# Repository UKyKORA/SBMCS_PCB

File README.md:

# Small Bot Motor Control Shield
This PCB makes building an advanced robot very simple. An onboard 32 bit ARM processor coordinates the control of 2 motors, as well as monitoring encoders on these motors for wheel odometry for the robot. There is a 9 axis IMU on the board to provide inertial odometry as well. a 5v @5A regulator provides enough power for most single board computers

### Board renders

### Assembled boards

### Demonstration

[https://youtu.be/KzK6t1kKt98](https://youtu.be/KzK6t1kKt98)

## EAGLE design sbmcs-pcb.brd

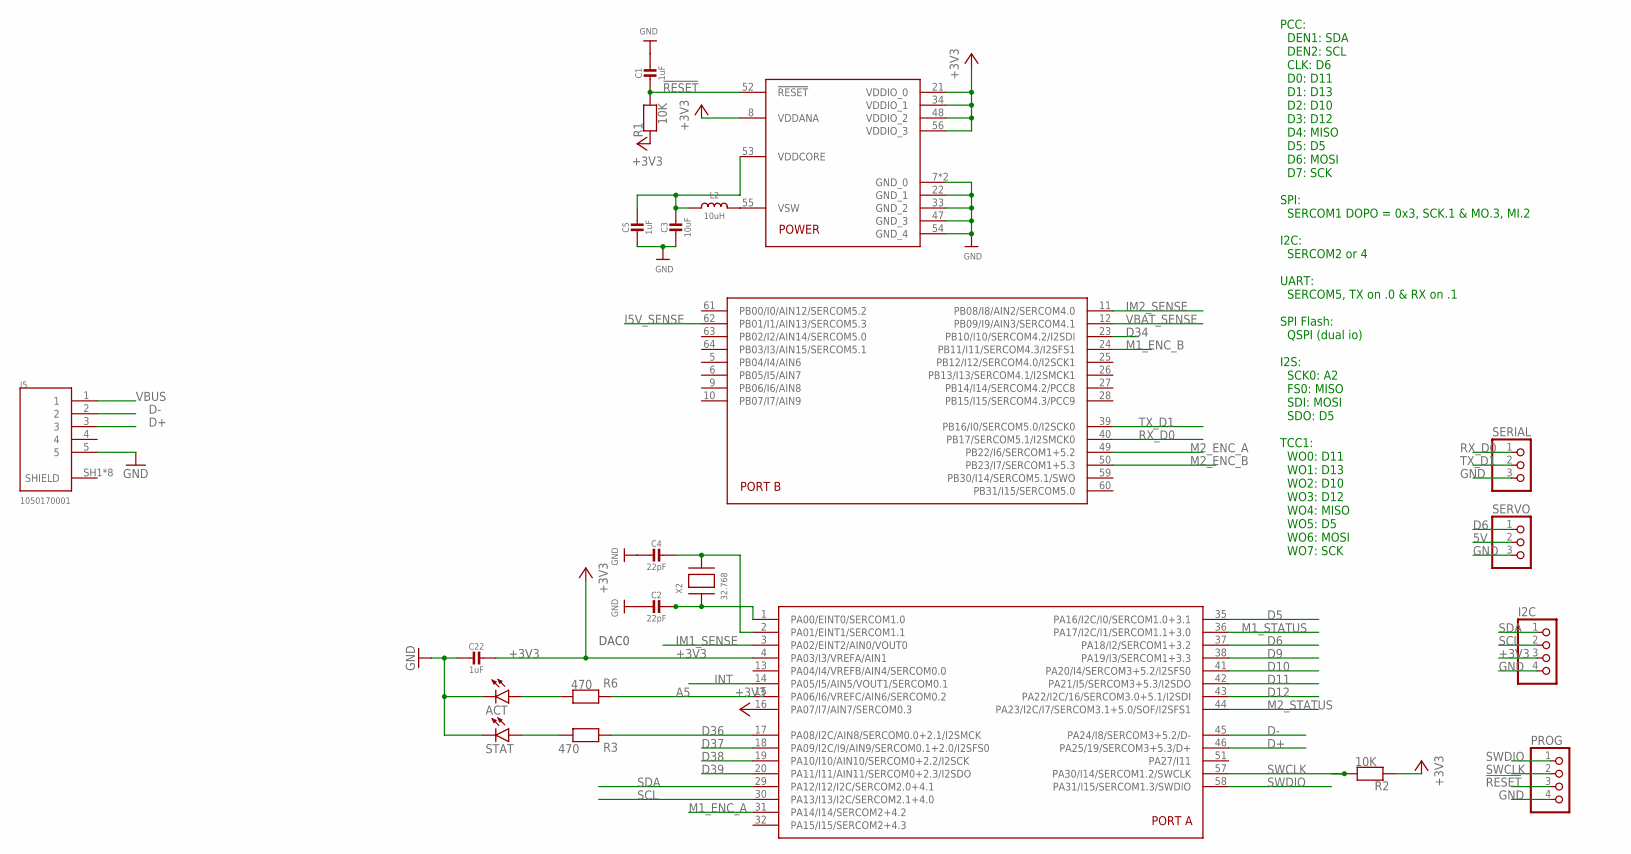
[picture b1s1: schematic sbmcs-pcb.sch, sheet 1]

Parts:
ACT: LEDCHIPLED_0805; CHIPLED_0805
C1, C5, C22: 1uF; 0603-NO
C2, C4: 22pF; 0603-NO
C3: 10uF; 0805-NO
I2C: PINHD-1X4; 1X04
J5: 1050170001; MOLEX_1050170001
L2: 10uH; INDUCTOR_1007
PROG: PINHD-1X4; 1X04
R1, R2: 10K; 0603-NO
R3, R6: 470; 0603-NO
SERIAL: PINHD-1X3; 1X03
SERVO: PINHD-1X3; 1X03
STAT: LEDCHIPLED_0805; CHIPLED_0805
U4: ATSAMD51J; PQFN64-1
X2: 32.768; XTAL3215

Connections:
5V: SERVO.2; also elsewhere on the board
!RESET: C1.2, PROG.3, R1.2, U4.52 (!RESET)
+3V3: C22.1, I2C.3, R1.1, R2.1, U4.4 (PA03/I3/VREFA/AIN1), U4.8 (VDDANA), U4.16 (PA07/I7/AIN7/SERCOM0.3), U4.21 (VDDIO_0), U4.34 (VDDIO_1), U4.48 (VDDIO_2), U4.56 (VDDIO_3); also elsewhere on the board
A5: R6.1, U4.15 (PA06/I6/VREFC/AIN6/SERCOM0.2)
D5: U4.35 (PA16/I2C/I0/SERCOM1.0+3.1)
D6: SERVO.1, U4.37 (PA18/I2/SERCOM1+3.2)
D9: U4.38 (PA19/I3/SERCOM1+3.3); also elsewhere on the board
D10: U4.41 (PA20/I4/SERCOM3+5.2/I2SFS0); also elsewhere on the board
D11: U4.42 (PA21/I5/SERCOM3+5.3/I2SDO); also elsewhere on the board
D12: U4.43 (PA22/I2C/16/SERCOM3.0+5.1/I2SDI); also elsewhere on the board
D34: U4.23 (PB10/I10/SERCOM4.2/I2SDI); also elsewhere on the board
D36: R3.1, U4.17 (PA08/I2C/AIN8/SERCOM0.0+2.1/I2SMCK)
D37: U4.18 (PA09/I2C/I9/AIN9/SERCOM0.1+2.0/I2SFS0); also elsewhere on the board
D38: U4.19 (PA10/I10/AIN10/SERCOM0+2.2/I2SCK); also elsewhere on the board
D39: U4.20 (PA11/I11/AIN11/SERCOM0+2.3/I2SDO); also elsewhere on the board
D+: J5.3, U4.46 (PA25/19/SERCOM3+5.3/D+)
D-: J5.2, U4.45 (PA24/I8/SERCOM3+5.2/D-)
GND: ACT.C, C1.1, C2.2, C3.2, C4.2, C5.2, C22.2, I2C.4, J5.5, PROG.4, SERIAL.3, SERVO.3, STAT.C, U4.7 (GND_0), U4.22 (GND_1), U4.33 (GND_2), U4.47 (GND_3), U4.54 (GND_4), U4.EXP (GND_0); also elsewhere on the board
I5V_SENSE: U4.62 (PB01/I1/AIN13/SERCOM5.3); also elsewhere on the board
IM1_SENSE: U4.3 (PA02/EINT2/AIN0/VOUT0); also elsewhere on the board
IM2_SENSE: U4.11 (PB08/I8/AIN2/SERCOM4.0); also elsewhere on the board
INT: U4.14 (PA05/I5/AIN5/VOUT1/SERCOM0.1); also elsewhere on the board
M1_ENC_A: U4.31 (PA14/I14/SERCOM2+4.2); also elsewhere on the board
M1_ENC_B: U4.24 (PB11/I11/SERCOM4.3/I2SFS1); also elsewhere on the board
M1_STATUS: U4.36 (PA17/I2C/I1/SERCOM1.1+3.0); also elsewhere on the board
M2_ENC_A: U4.49 (PB22/I6/SERCOM1+5.2); also elsewhere on the board
M2_ENC_B: U4.50 (PB23/I7/SERCOM1+5.3); also elsewhere on the board
M2_STATUS: U4.44 (PA23/I2C/I7/SERCOM3.1+5.0/SOF/I2SFS1); also elsewhere on the board
unnamed: R3.2, STAT.A
unnamed: ACT.A, R6.2
unnamed: C2.1, U4.1 (PA00/EINT0/SERCOM1.0), X2.P$1
unnamed: C4.1, U4.2 (PA01/EINT1/SERCOM1.1), X2.P$2
unnamed: L2.P$2 (2), U4.55 (VSW)
RX_D0: SERIAL.1, U4.40 (PB17/SERCOM5.1/I2SMCK0)
SCL: I2C.2, U4.30 (PA13/I13/I2C/SERCOM2.1+4.0); also elsewhere on the board
SDA: I2C.1, U4.29 (PA12/I12/I2C/SERCOM2.0+4.1); also elsewhere on the board
SWCLK: PROG.2, R2.2, U4.57 (PA30/I14/SERCOM1.2/SWCLK)
SWDIO: PROG.1, U4.58 (PA31/I15/SERCOM1.3/SWDIO)
TX_D1: SERIAL.2, U4.39 (PB16/I0/SERCOM5.0/I2SCK0)
VBAT_SENSE: U4.12 (PB09/I9/AIN3/SERCOM4.1); also elsewhere on the board
VBUS: J5.1; also elsewhere on the board
VDDCORE1: C3.1, C5.1, L2.P$1 (1), U4.53 (VDDCORE)

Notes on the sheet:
PCC: DEN1: SDA DEN2: SCL CLK: D6 D0: D11 D1: D13 D2: D10 D3: D12 D4: MISO D5: D5 D6: MOSI D7: SCK SPI: SERCOM1 DOPO = 0x3, SCK.1 & MO.3, MI.2 I2C: SERCOM2 or 4 UART: SERCOM5, TX on .0 & RX on .1 SPI Flash: QSPI (dual io) I2S: SCK0: A2 FS0: MISO SDI: MOSI SDO: D5 TCC1: WO0: D11 WO1: D13 WO2: D10 WO3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
DAC0

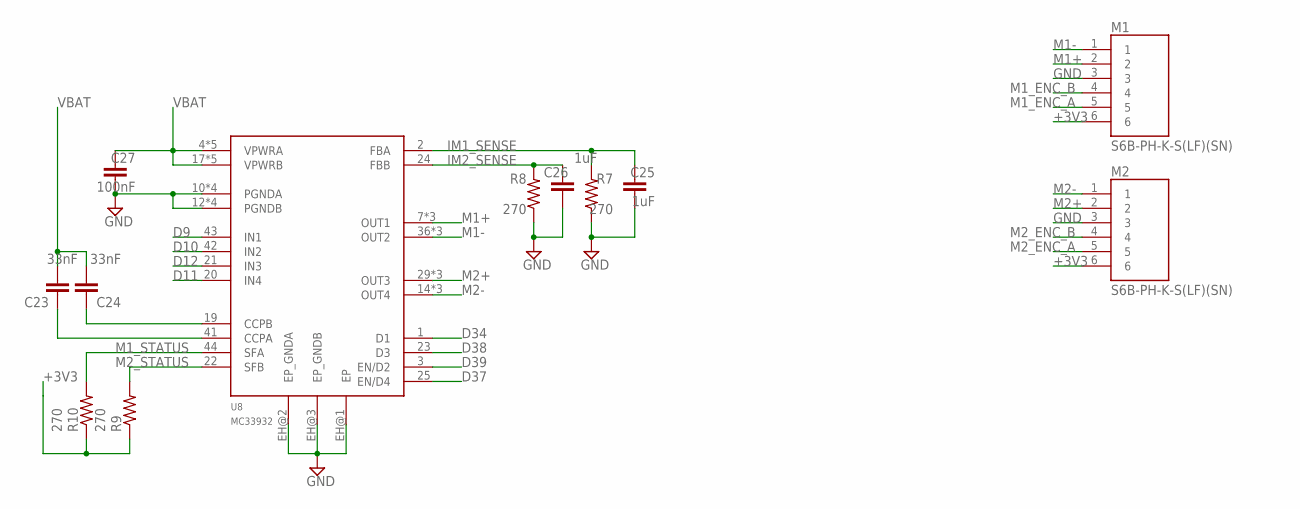
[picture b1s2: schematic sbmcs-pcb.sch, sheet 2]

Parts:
C23, C24: 33nF; C0603
C25, C26: 1uF; C0603
C27: 100nF; C0603
M1, M2: S6B-PH-K-S(LF)(SN); JST_S6B-PH-K-S(LF)(SN)
R7, R8, R9, R10: 270; R0603
U8: MC33932; HSOP44

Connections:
+3V3: M1.6, M2.6, R9.1, R10.1; also elsewhere on the board
D9: U8.43 (IN1); also elsewhere on the board
D10: U8.42 (IN2); also elsewhere on the board
D11: U8.20 (IN4); also elsewhere on the board
D12: U8.21 (IN3); also elsewhere on the board
D34: U8.1 (D1); also elsewhere on the board
D37: U8.25 (EN/D4); also elsewhere on the board
D38: U8.23 (D3); also elsewhere on the board
D39: U8.3 (EN/D2); also elsewhere on the board
GND: C25.1, C26.1, C27.1, M1.3, M2.3, R7.1, R8.1, U8.10 (PGNDA), U8.11 (PGNDA), U8.12 (PGNDB), U8.13 (PGNDB), U8.32 (PGNDB), U8.33 (PGNDB), U8.34 (PGNDA), U8.35 (PGNDA), U8.EH@1 (EP), U8.EH@2 (EP_GNDA), U8.EH@3 (EP_GNDB); also elsewhere on the board
IM1_SENSE: C25.2, R7.2, U8.2 (FBA); also elsewhere on the board
IM2_SENSE: C26.2, R8.2, U8.24 (FBB); also elsewhere on the board
M1+: M1.2, U8.7 (OUT1), U8.8 (OUT1), U8.9 (OUT1)
M1-: M1.1, U8.36 (OUT2), U8.37 (OUT2), U8.38 (OUT2)
M1_ENC_A: M1.5; also elsewhere on the board
M1_ENC_B: M1.4; also elsewhere on the board
M1_STATUS: R10.2, U8.44 (SFA); also elsewhere on the board
M2+: M2.2, U8.29 (OUT3), U8.30 (OUT3), U8.31 (OUT3)
M2-: M2.1, U8.14 (OUT4), U8.15 (OUT4), U8.16 (OUT4)
M2_ENC_A: M2.5; also elsewhere on the board
M2_ENC_B: M2.4; also elsewhere on the board
M2_STATUS: R9.2, U8.22 (SFB); also elsewhere on the board
unnamed: C24.1, U8.41 (CCPA)
unnamed: C23.1, U8.19 (CCPB)
VBAT: C23.2, C24.2, C27.2, U8.4 (VPWRA), U8.5 (VPWRA), U8.6 (VPWRA), U8.17 (VPWRB), U8.18 (VPWRB), U8.26 (VPWRB), U8.27 (VPWRB), U8.28 (VPWRB), U8.39 (VPWRA), U8.40 (VPWRA); also elsewhere on the board

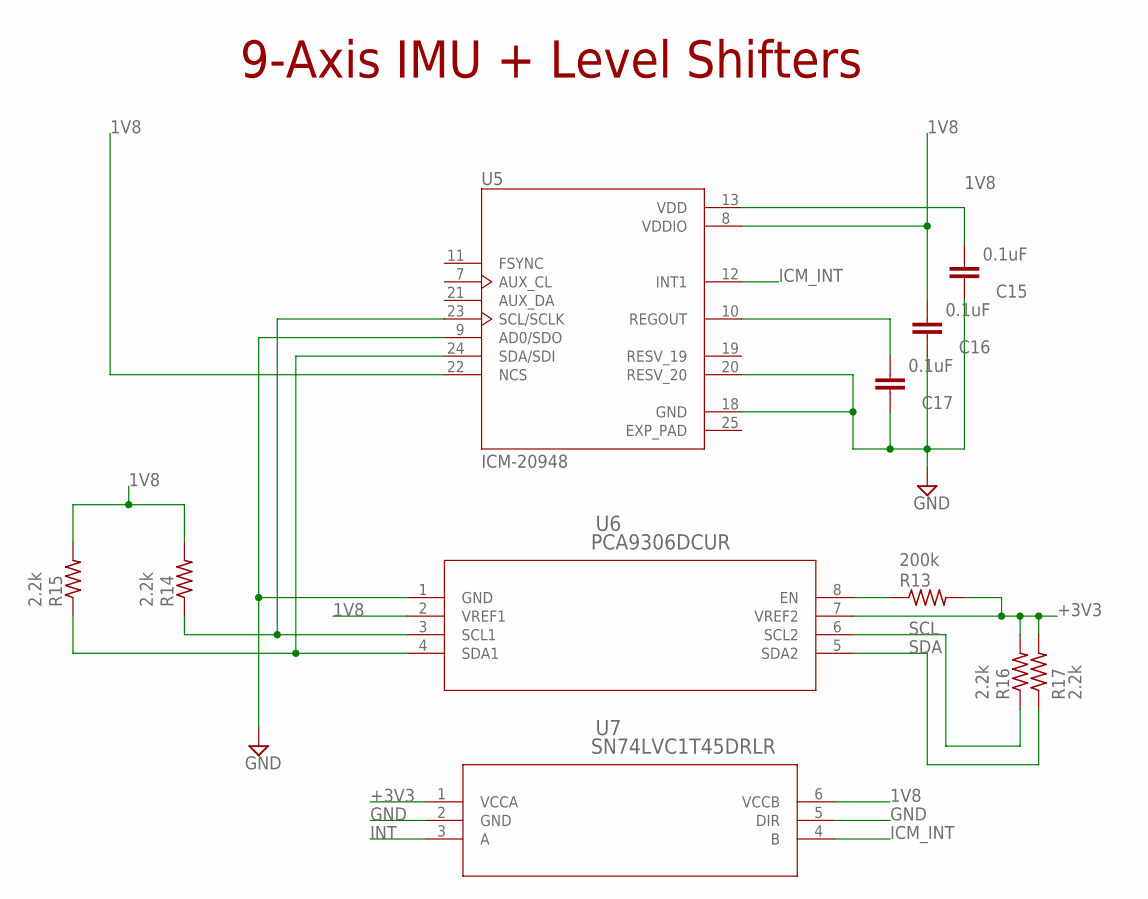
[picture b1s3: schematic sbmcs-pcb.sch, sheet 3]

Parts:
C15, C16, C17: 0.1uF; C0603
R13: 200k; R0603
R14, R15, R16, R17: 2.2k; R0603
U5: ICM-20948; QFN40P300X300X105-25N
U6: PCA9306DCUR; DCU8
U7: SN74LVC1T45DRLR; DRL6

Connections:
1V8: C15.2, C16.2, R14.2, R15.2, U5.8 (VDDIO), U5.13 (VDD), U5.22 (NCS), U6.2 (VREF1), U7.6 (VCCB); also elsewhere on the board
+3V3: R13.2, R16.2, R17.2, U6.7 (VREF2), U7.1 (VCCA); also elsewhere on the board
EXP_PAD: U5.25 (EXP_PAD)
GND: C15.1, C16.1, C17.1, U5.9 (AD0/SDO), U5.18 (GND), U5.20 (RESV_20), U6.1 (GND), U7.2 (GND), U7.5 (DIR); also elsewhere on the board
ICM_INT: U5.12 (INT1), U7.4 (B)
INT: U7.3 (A); also elsewhere on the board
unnamed: R13.1, U6.8 (EN)
unnamed: C17.2, U5.10 (REGOUT)
unnamed: R14.1, U5.23 (SCL/SCLK), U6.3 (SCL1)
unnamed: R15.1, U5.24 (SDA/SDI), U6.4 (SDA1)
SCL: R16.1, U6.6 (SCL2); also elsewhere on the board
SDA: R17.1, U6.5 (SDA2); also elsewhere on the board

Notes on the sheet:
9-Axis IMU + Level Shifters

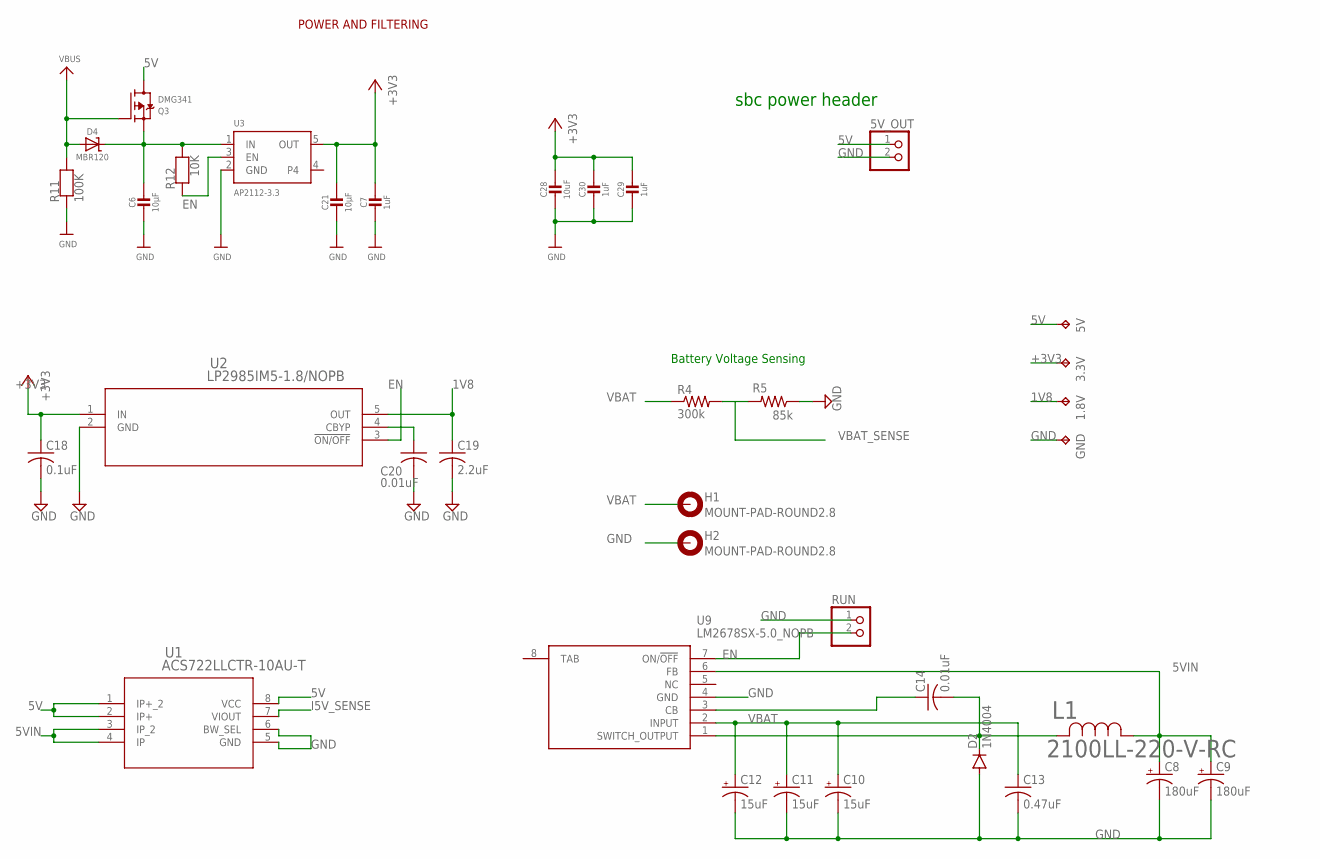
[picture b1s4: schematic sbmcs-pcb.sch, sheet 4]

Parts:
1.8V, 3.3V, 5V: TPTP20R; TP20R
5V_OUT: PINHD-1X2; 1X02
C6, C21: 10µF; 0805-NO
C7, C29, C30: 1uF; 0603-NO
C8, C9: 180uF; E2,5-6
C10, C11, C12: 15uF; E2,5-6
C13: 0.47uF; C0603
C14, C20: 0.01uF; C0603
C18: 0.1uF; C0603
C19: 2.2uF; C0603
C28: 10uF; 0805-NO
D2: 1N4004; DO41-10
D4: MBR120; SOD-123
GND: TPTP20R; TP20R
H1, H2: MOUNT-PAD-ROUND2.8; 2,8-PAD
L1: 2100LL-220-V-RC; IND_2100LL_42_V
Q3: DMG341; SOT23-R
R4: 300k; R0603
R5: 85k; R0603
R11: 100K; 0603-NO
R12: 10K; 0603-NO
RUN: PINHD-1X2; 1X02
U1: ACS722LLCTR-10AU-T; SOICN-8_ALM
U2: LP2985IM5-1.8/NOPB; MF05A
U3: AP2112-3.3; SOT23-5
U9: LM2678SX-5.0_NOPB; KTW0007B

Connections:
1V8: 1.8V.TP, C19.1, U2.5 (OUT); also elsewhere on the board
5V: 5V.TP, 5V_OUT.1, Q3.3 (D), U1.1 (IP+_2), U1.2 (IP+), U1.8 (VCC); also elsewhere on the board
5VIN: C8.+, C9.+, L1.1, U1.3 (IP_2), U1.4 (IP), U9.6 (FB)
+3V3: 3.3V.TP, C7.1, C18.1, C21.1, C28.1, C29.1, C30.1, U2.1 (IN), U3.5 (OUT); also elsewhere on the board
EN: R12.1, RUN.2, U2.3 (!ON/OFF), U3.3 (EN), U9.7 (ON/!OFF)
GND: 5V_OUT.2, C6.2, C7.2, C8.-, C9.-, C10.-, C11.-, C12.-, C13.2, C18.2, C19.2, C20.2, C21.2, C28.2, C29.2, C30.2, D2.A, GND.TP, H2.B2,8, R5.1, R11.1, RUN.1, U1.5 (GND), U1.6 (BW_SEL), U2.2 (GND), U3.2 (GND), U9.4 (GND); also elsewhere on the board
I5V_SENSE: U1.7 (VIOUT); also elsewhere on the board
unnamed: C20.1, U2.4 (CBYP)
unnamed: C14.1, U9.3 (CB)
unnamed: C14.2, D2.C, L1.2, U9.1 (SWITCH_OUTPUT)
VBAT: C10.+, C11.+, C12.+, C13.1, H1.B2,8, R4.1, U9.2 (INPUT); also elsewhere on the board
VBAT_SENSE: R4.2, R5.2; also elsewhere on the board
VBUS: D4.A, Q3.1 (G), R11.2; also elsewhere on the board
VHI: C6.1, D4.C, Q3.2 (S), R12.2, U3.1 (IN)

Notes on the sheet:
Battery Voltage Sensing
POWER AND FILTERING
sbc power header

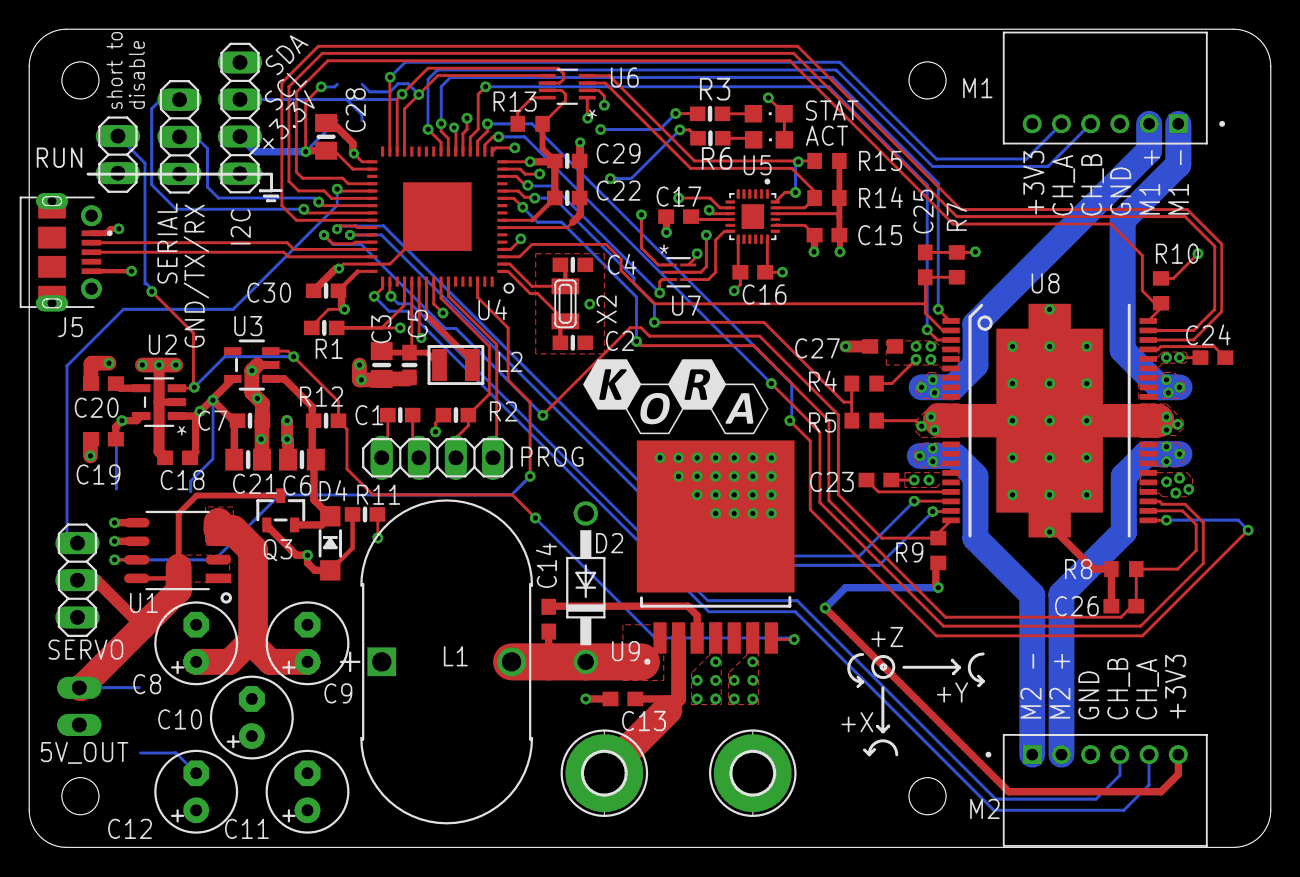
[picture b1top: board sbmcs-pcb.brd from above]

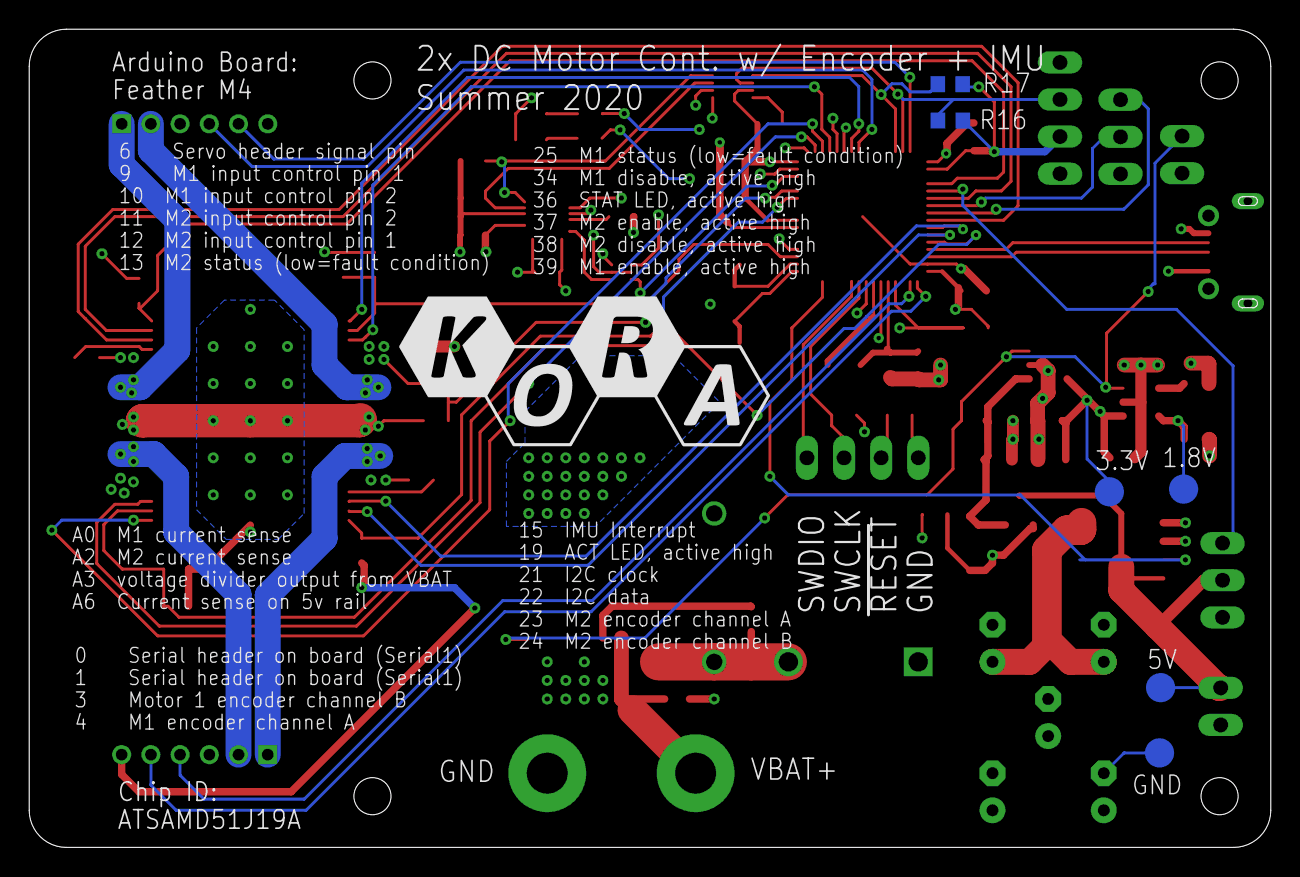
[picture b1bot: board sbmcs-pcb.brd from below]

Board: 4 copper layers, 85.0 x 56.0 mm, 79 parts (6 on the bottom side), 60 nets.

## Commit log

2020-07-14 initial commit of v1 SBMCS
    * Eagle files for schematic and board layout
    * SMT and PTH partslists
    * Digikey cart with board components
    * Top/bottom renderings of board
    * Gerbers
    * Outline of SBMCS hardware manual
2020-09-04 add image of assembled board

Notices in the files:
parts and their libraries:
microbuilder: This work is placed in the public domain, and may be freely used for commercial and non-commercial work with the following conditions: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
COPYRIGHT: Copyright (C) 2018 Accelerated Designs. All rights reserved
